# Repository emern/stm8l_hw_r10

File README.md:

# stm8l_hw_r10

## About

Project for a simple breakout board for STMicroelectronics STM8L151C2T6 ultra low-power microcontroller designed with KiCAD version 5.1.3.

## Features

This breakout has the following features:

* Induvidual 5v and 3.3v power bus enable/disable
* USB 2.0 Type-C serial interface
* ST Link programming header
* Full GPIO pinout
* External RTC over I2C (DS1307Z)
* Power and Status LED's
* 5v-12v main power inputs
* M2.5 screw mounting holes

## Requirements

* KiCAD 5.1.3
* [FTDI drivers needed for USB-serial interface](https://ftdichip.com/drivers/)
* Serial monitor such as [PuTTY](https://www.putty.org/)
* [Example Firmware](https://github.com/emern/stm8l_fw_r10)

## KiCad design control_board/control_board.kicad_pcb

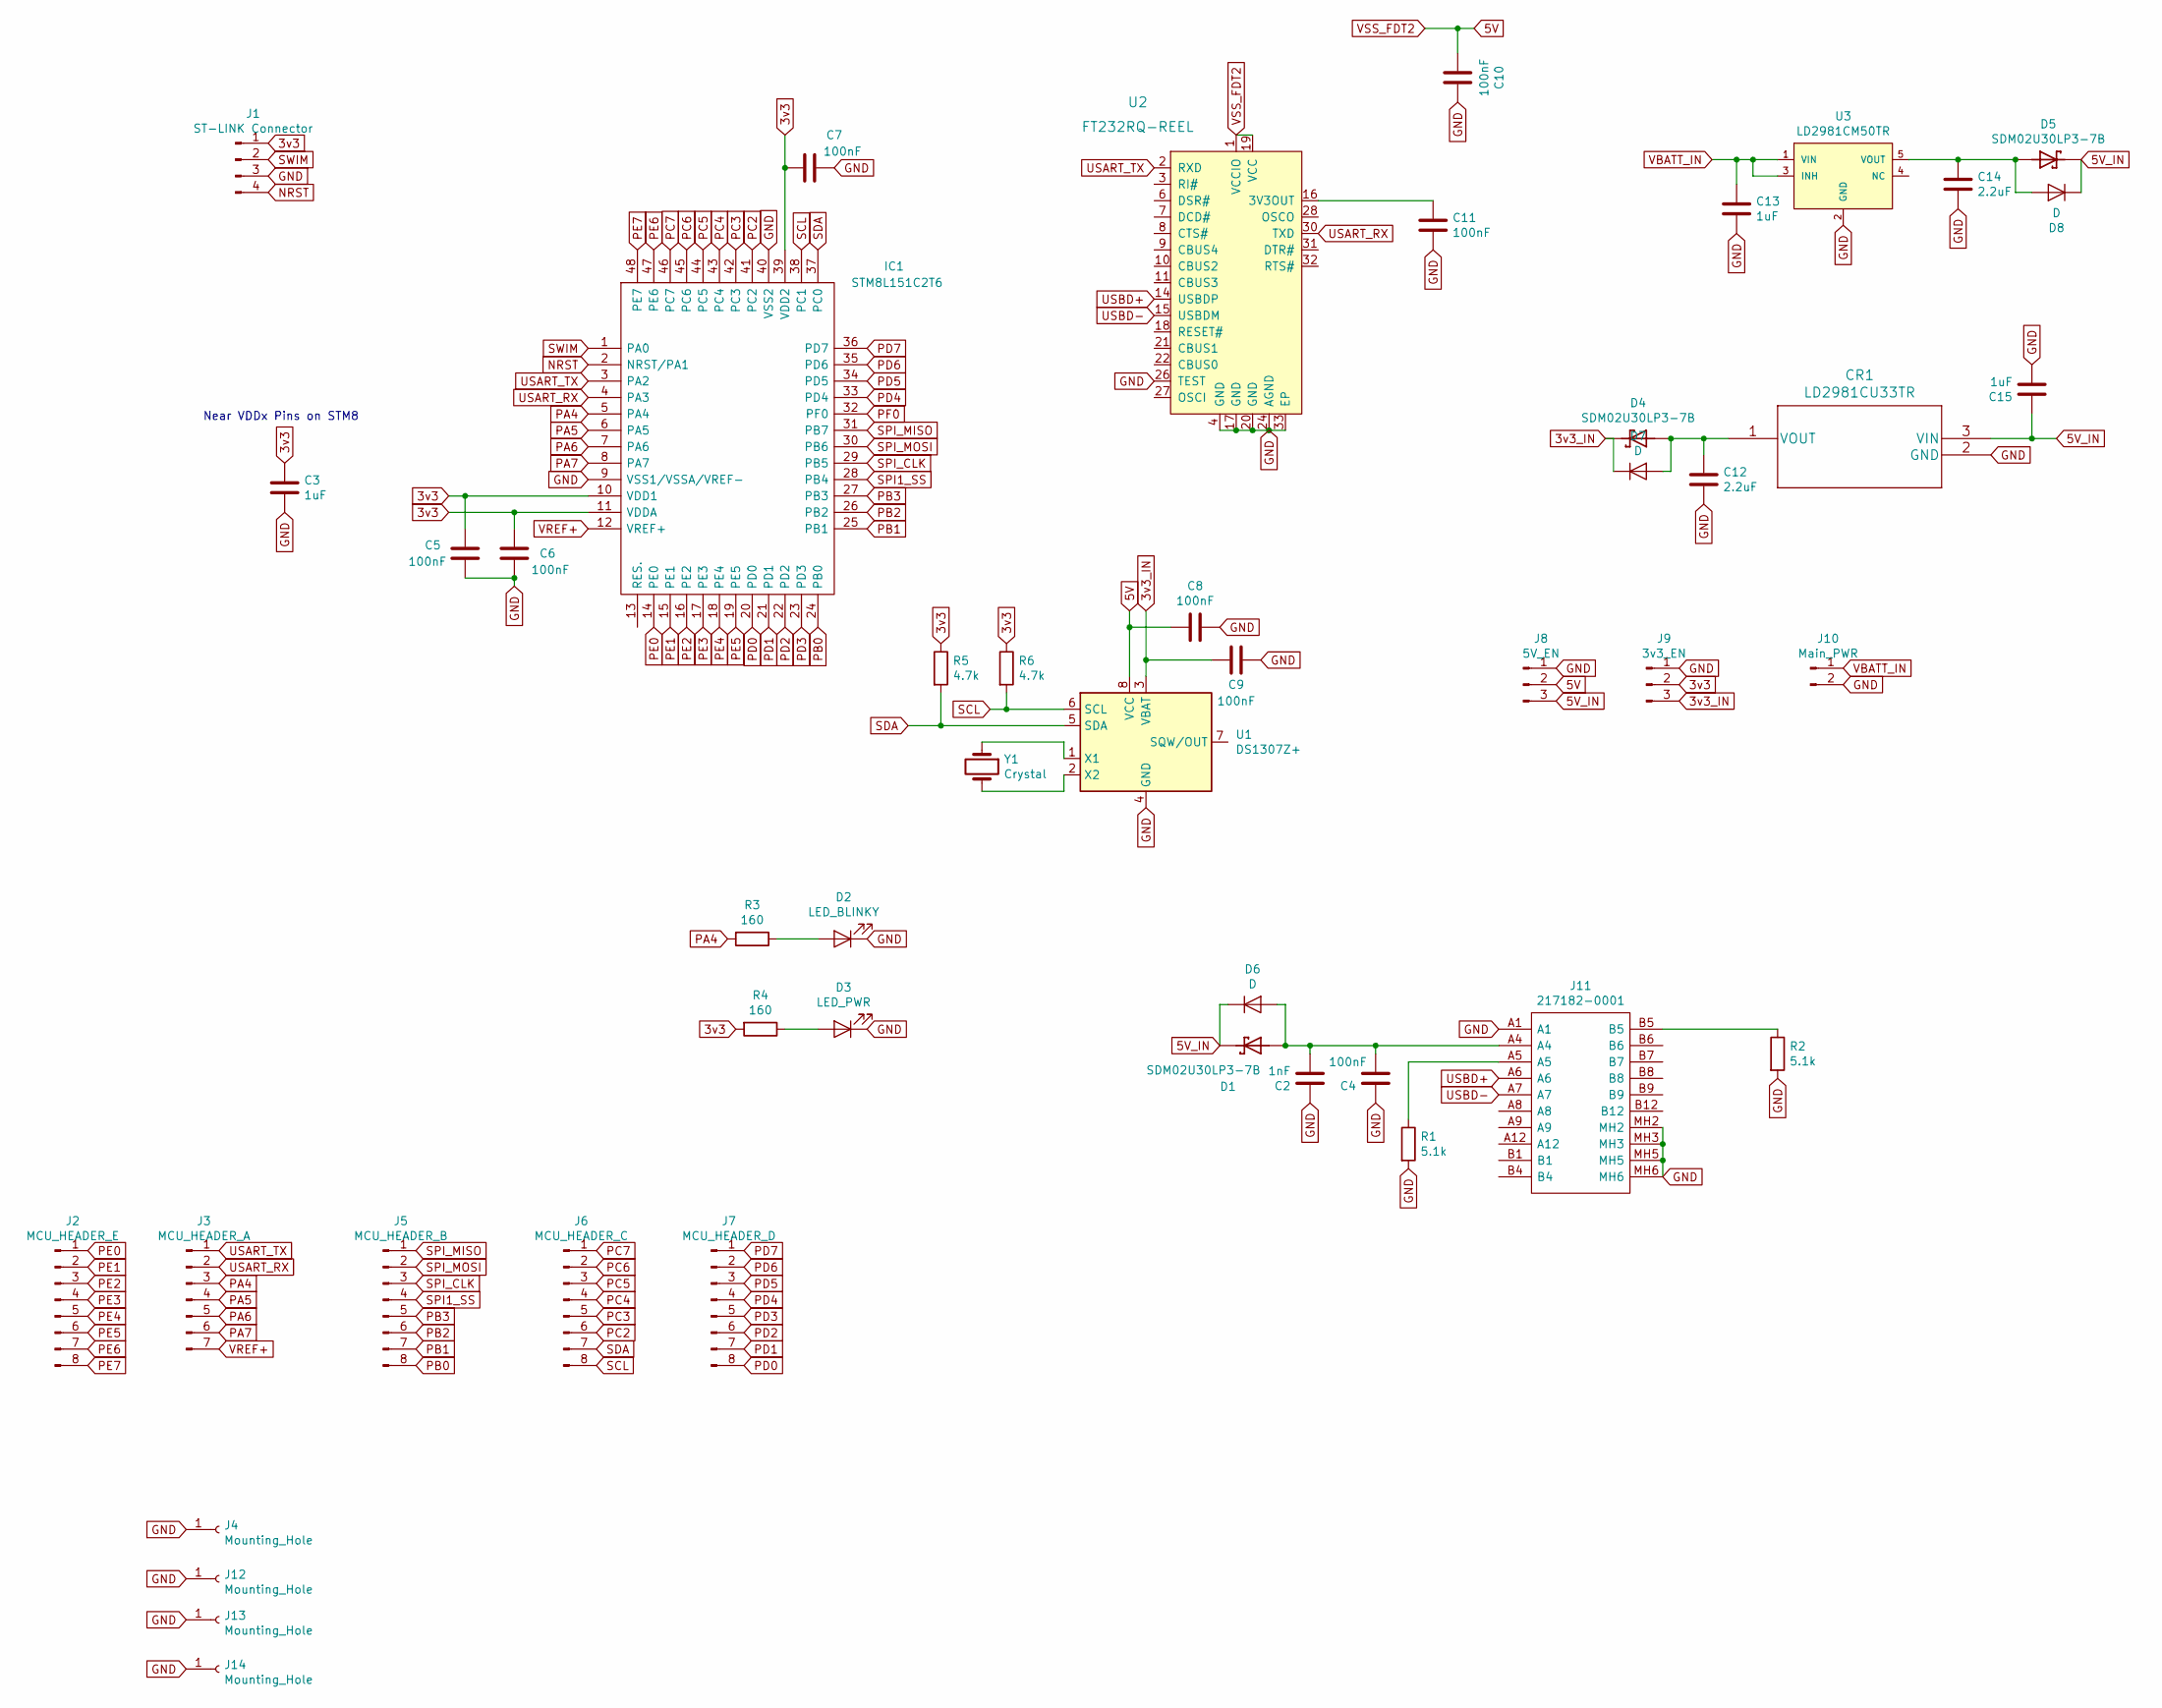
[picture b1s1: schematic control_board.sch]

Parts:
C2: 1nF; C_0805_2012Metric
C3, C13, C15: 1uF; C_1206_3216Metric
C4, C5, C6, C7, C8, C9, C10, C11: 100nF; C_0805_2012Metric
C12, C14: 2.2uF; C_0805_2012Metric
CR1: LD2981CU33TR; SOT-89-3
D1, D4, D5: SDM02U30LP3-7B; DIODFN62X32X35-2N; PARTREV 5
D2: LED_BLINKY; LED_0402_1005Metric
D3: LED_PWR; LED_0402_1005Metric
D6, D7, D8: D; D_0603_1608Metric
IC1: STM8L151C2T6; LQFP-48_7x7mm_P0.5mm; Manufacturer_Part_Number STM8L151C6T6; Mouser Part Number 511-STM8L151C6T6
J1: ST-LINK Connector; PinHeader_1x04_P2.54mm_Vertical
J2: MCU_HEADER_E; PinHeader_1x08_P2.54mm_Vertical
J3: MCU_HEADER_A; PinHeader_1x07_P2.54mm_Vertical
J4, J12, J13, J14: Mounting_Hole; MountingHole_2.7mm_M2.5_Pad
J5: MCU_HEADER_B; PinHeader_1x08_P2.54mm_Vertical
J6: MCU_HEADER_C; PinHeader_1x08_P2.54mm_Vertical
J7: MCU_HEADER_D; PinHeader_1x08_P2.54mm_Vertical
J8: 5V_EN; PinHeader_1x03_P2.54mm_Vertical
J9: 3v3_EN; PinHeader_1x03_P2.54mm_Vertical
J10: Main_PWR; PinHeader_1x02_P2.54mm_Vertical
J11: 217182-0001; 2171820001; Manufacturer_Part_Number 217182-0001; Mouser Part Number 538-217182-0001
R1, R2: 5.1k; R_1206_3216Metric
R3, R4: 160; R_1206_3216Metric
R5, R6: 4.7k; R_0402_1005Metric
U1: DS1307Z+; SOIC-8_3.9x4.9mm_P1.27mm
U2: FT232RQ-REEL; QFN-32-1EP_5x5mm; MPN FT232RQ-REEL; Digi-Key_PN 768-1008-1-ND
U3: LD2981CM50TR; SOT-23-5
Y1: Crystal; Crystal_SMD_3215-2Pin_3.2x1.5mm

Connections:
3v3: C3.1, C5.2, C6.1, C7.1, IC1.10 (VDD1), IC1.11 (VDDA), IC1.39 (VDD2), J1.1, J9.2, R4.2, R5.1, R6.1
3v3_IN: C9.2, D4.C, D7.1 (K), J9.3, U1.3 (VBAT)
5V: C8.2, C10.2, J8.2, U1.8 (VCC), U2.1 (VCCIO), U2.19 (VCC)
5V_IN: C15.1, CR1.3 (VIN), D1.C, D5.C, D6.1 (K), D8.1 (K), J8.3
GND: C2.1, C3.2, C4.1, C5.1, C6.2, C7.2, C8.1, C9.1, C10.1, C11.2, C12.2, C13.2, C14.2, C15.2, CR1.2 (GND), D2.1 (K), D3.1 (K), IC1.9 (VSS1/VSSA/VREF-), IC1.40 (VSS2), J1.3, J4.1, J8.1, J9.1, J10.2, J11.A1, J11.MH2, J11.MH3, J11.MH5, J11.MH6, J12.1, J13.1, J14.1, R1.2, R2.2, U1.4 (GND), U2.4 (GND), U2.17 (GND), U2.20 (GND), U2.24 (AGND), U2.26 (TEST), U2.33 (EP), U3.2 (GND)
NRST: IC1.2 (NRST/PA1), J1.4
unnamed: C2.2, C4.2, D1.A, D6.2 (A), J11.A4
unnamed: C11.1, U2.16 (3V3OUT)
unnamed: C12.1, CR1.1 (VOUT), D4.A, D7.2 (A)
unnamed: C14.1, D5.A, D8.2 (A), U3.5 (VOUT)
unnamed: D2.2 (A), R3.1
unnamed: D3.2 (A), R4.1
unnamed: J11.A5, R1.1
unnamed: J11.B5, R2.1
unnamed: U1.1 (X1), Y1.1
unnamed: U1.2 (X2), Y1.2
PA4: IC1.5 (PA4), J3.3, R3.2
PA5: IC1.6 (PA5), J3.4
PA6: IC1.7 (PA6), J3.5
PA7: IC1.8 (PA7), J3.6
PB0: IC1.24 (PB0), J5.8
PB1: IC1.25 (PB1), J5.7
PB2: IC1.26 (PB2), J5.6
PB3: IC1.27 (PB3), J5.5
PC2: IC1.41 (PC2), J6.6
PC3: IC1.42 (PC3), J6.5
PC4: IC1.43 (PC4), J6.4
PC5: IC1.44 (PC5), J6.3
PC6: IC1.45 (PC6), J6.2
PC7: IC1.46 (PC7), J6.1
PD0: IC1.20 (PD0), J7.8
PD1: IC1.21 (PD1), J7.7
PD2: IC1.22 (PD2), J7.6
PD3: IC1.23 (PD3), J7.5
PD4: IC1.33 (PD4), J7.4
PD5: IC1.34 (PD5), J7.3
PD6: IC1.35 (PD6), J7.2
PD7: IC1.36 (PD7), J7.1
PE0: IC1.14 (PE0), J2.1
PE1: IC1.15 (PE1), J2.2
PE2: IC1.16 (PE2), J2.3
PE3: IC1.17 (PE3), J2.4
PE4: IC1.18 (PE4), J2.5
PE5: IC1.19 (PE5), J2.6
PE6: IC1.47 (PE6), J2.7
PE7: IC1.48 (PE7), J2.8
PF0: IC1.32 (PF0)
SCL: IC1.38 (PC1), J6.8, R6.2, U1.6 (SCL)
SDA: IC1.37 (PC0), J6.7, R5.2, U1.5 (SDA)
SPI1_SS: IC1.28 (PB4), J5.4
SPI_CLK: IC1.29 (PB5), J5.3
SPI_MISO: IC1.31 (PB7), J5.1
SPI_MOSI: IC1.30 (PB6), J5.2
SWIM: IC1.1 (PA0), J1.2
USART_RX: IC1.4 (PA3), J3.2, U2.30 (TXD)
USART_TX: IC1.3 (PA2), J3.1, U2.2 (RXD)
USBD+: J11.A6, U2.14 (USBDP)
USBD-: J11.A7, U2.15 (USBDM)
VBATT_IN: C13.1, J10.1, U3.1 (VIN), U3.3 (INH)
VREF+: IC1.12 (VREF+), J3.7

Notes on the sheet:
Near VDDx Pins on STM8

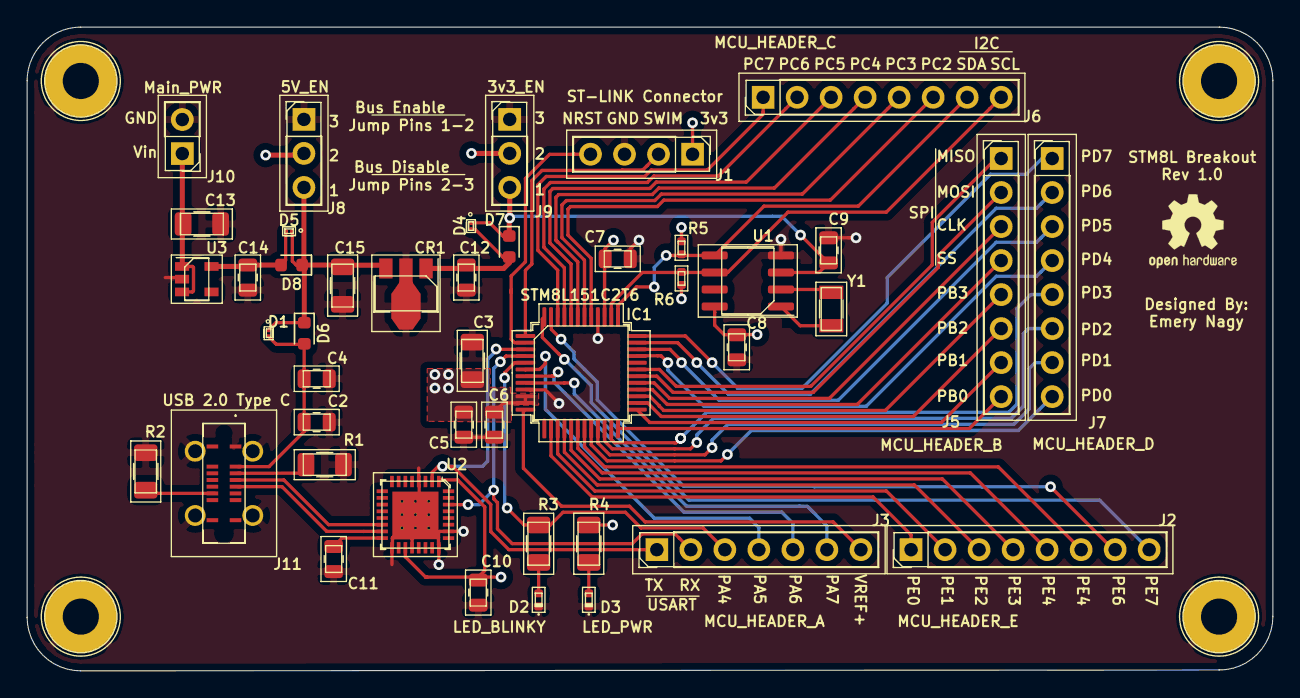
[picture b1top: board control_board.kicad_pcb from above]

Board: 4 copper layers, 93.0 x 48.1 mm, 48 parts (0 on the bottom side), 59 nets.

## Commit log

2021-11-28 add rev1.0 hardware
2022-01-03 update main regulator input
